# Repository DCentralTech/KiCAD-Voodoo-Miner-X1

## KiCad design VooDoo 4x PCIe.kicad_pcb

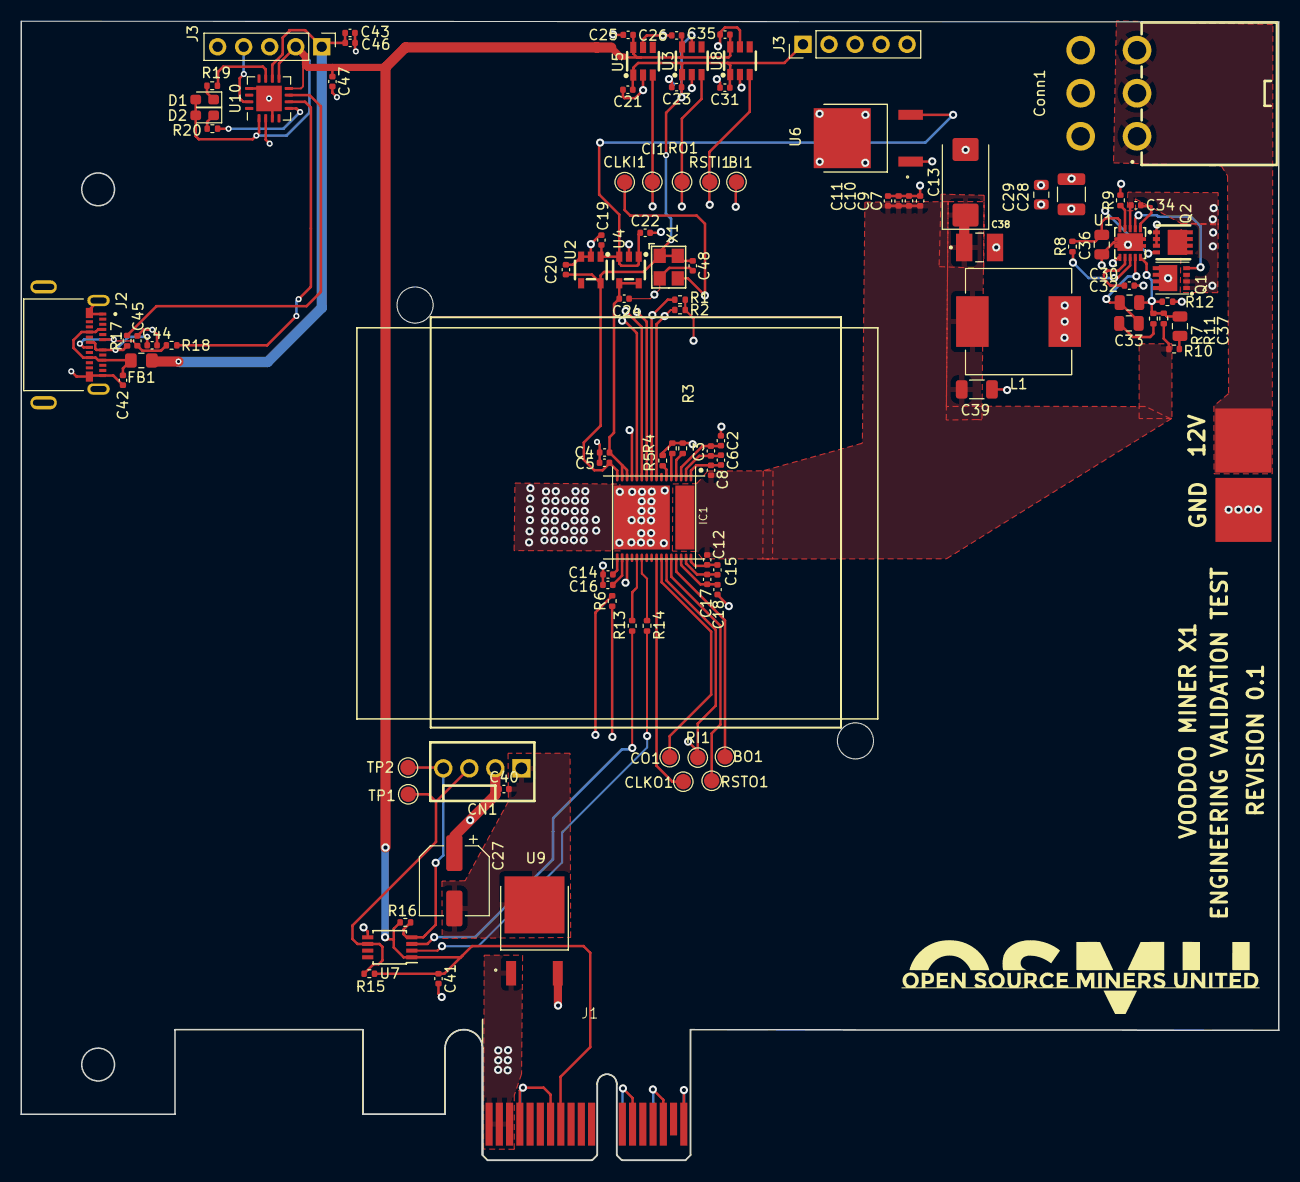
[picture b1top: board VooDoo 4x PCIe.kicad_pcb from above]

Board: 4 copper layers, 122.7 x 111.2 mm, 104 parts (1 on the bottom side), 54 nets.

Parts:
BI1: TestPoint; TestPoint_Pad_D1.5mm
BO1: TestPoint; TestPoint_Pad_D1.5mm
C1: 470pF; C_0402_1005Metric
C2, C3, C4, C5, C6, C8, C10, C11, C12, C14, C15, C16, C17, C18: 587-5514-1-ND; C_0402_1005Metric
C7, C9, C21, C23, C25, C26, C31, C35, C40, C41, C48: 311-3342-1-ND; C_0402_1005Metric
C13: 330uF; CP_EIA-7343-31_Kemet-D_Pad2.25x2.55mm_HandSolder
C19, C22, C24: 1uF; C_0402_1005Metric
C20: 2.2uF; C_0402_1005Metric
C27: 220uF; CP_Elec_6.3x7.7
C28: 10uF; C_1210_3225Metric
C29: 1uF; C_0805_2012Metric
C30: 3.3nF; C_0402_1005Metric
C32: 270pF; C_0805_2012Metric
C33: 1.8nF; C_0805_2012Metric
C34: 0.1uF; C_0402_1005Metric
C36: 4.7uF; C_0805_2012Metric
C37: 680pF; C_0805_2012Metric
C38: 220uF; CAP_2R5TPE220MFGB
C39: 22uF; C_1206_3216Metric
C42: 10nF; C_0402_1005Metric
C43, C47: 100nF; C_0402_1005Metric
C44, C45: 47pF; C_0402_1005Metric
C46: 4.7uF; C_0402_1005Metric
CI1: TestPoint; TestPoint_Pad_D1.5mm
CLKI1: TestPoint; TestPoint_Pad_D1.5mm
CLKO1: TestPoint; TestPoint_Pad_D1.5mm
CN1: HF1004E; CONN-TH_4P-P2.54_HF1004E
CO1: TestPoint; TestPoint_Pad_D1.5mm
Conn1: CONN-TH_HAA420A-6AW
D1: RXLED; LED_0603_1608Metric_Pad1.05x0.95mm_HandSolder
D2: TXLED; LED_0603_1608Metric_Pad1.05x0.95mm_HandSolder
FB1: Ferrite_Bead; L_0805_2012Metric_Pad1.15x1.40mm_HandSolder
IC1: BM1397_mode1; BM1397
J1: PCIexpress_x1; PCIE1XSMALL
J2: USB_C_Receptacle_USB2.0; MOLEX_1054550101
J3, J3#2: Conn_01x05; PinHeader_1x05_P2.54mm_Vertical
L1: 330nH; L_Vishay_IHLP-4040
Q1: CSD17551Q3A; VSONP-8_L3.2-W3.0-P0.65-LS3.3-BL
Q2: CSD17575Q3; VSON-CLIP-8_L3.3-W3.3-P0.65-BL
R1, R2: 1k; R_0402_1005Metric
R3, R4, R5: 0; R_0402_1005Metric
R6, R11, R16: 10k; R_0402_1005Metric
R7: 4.12k; R_0402_1005Metric
R8: 100k; R_0402_1005Metric
R9: 5.9k; R_0402_1005Metric
R10: 1.62k; R_0402_1005Metric
R12: 6.65k; R_0402_1005Metric
R13, R14: 100; R_0402_1005Metric
R15: 5.6k; R_0402_1005Metric
R17, R18: 27R; R_0402_1005Metric
R19, R20: 270R; R_0402_1005Metric
RI1: TestPoint; TestPoint_Pad_D1.5mm
RO1: TestPoint; TestPoint_Pad_D1.5mm
RSTI1: TestPoint; TestPoint_Pad_D1.5mm
RSTO1: TestPoint; TestPoint_Pad_D1.5mm
TP1, TP2: TestPoint; TestPoint_Pad_D1.5mm
U1: TPS40305; VSON-10_L3.0-W3.0-P0.50-BL-EP_TPS62410DRCR
U2: LN1134A182MR-G; SOT-23-5_L3.0-W1.7-P0.95-LS2.8-BR
U3, U5, U8: SN74LVC1T45DBVR; SOT-23-6_L2.9-W1.6-P0.95-LS2.8-BR
U4: SGM2036-ADJYN5G/TR; SOT-23-5_L3.0-W1.7-P0.95-LS2.8-BR
U6, U9: VREG_L7805CDT-TR
U7: EMC2101-R; TSSOP-8_3x3mm_P0.65mm
U10: FT230XQ; QFN-16-1EP_4x4mm_P0.65mm_EP2.5x2.5mm
X1: OT322525MJBA4SL; OSC-SMD_4P-L3.2-W2.5-BL

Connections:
3V3: C25.1, C26.1, C35.1, C41.1, C47.1, D1.2 (A), D2.2 (A), J1.A9 (+3.3V), J1.A10 (+3.3V), J1.B8 (+3.3V), J3#2.2, R15.2, R16.2, U3.6 (VCCB), U5.6 (VCCB), U7.1 (VDD), U8.6 (VCCB), U10.1 (VCCIO), U10.8 (3V3OUT), U10.9 (~RESET)
5V: C19.1, C22.1, C27.1, C40.1, CN1.2, U2.1 (VIN), U4.1 (IN), U4.3 (EN), U6.2, U9.2
+12V: C28.1, C29.1, Conn1.1, Conn1.3, Conn1.5, Q1.5 (D), U1.1 (VDD), U6.1
/Asic/0V8: C4.1, C16.1, C24.1, IC1.14 (PLL_VDD), IC1.15 (VDDIO_08_0), IC1.18 (VDDIO_08_1), U4.4 (BP/FB), U4.5 (OUT)
/Asic/1V8: C5.1, C14.1, C20.1, C21.1, C23.1, C31.1, C48.2, IC1.16 (VDDIO_18_0), IC1.17 (VDDIO_18_1), J3.1, R6.2, U2.5 (VOUT), U3.1 (VCCA), U3.5 (DIR), U5.1 (VCCA), U8.1 (VCCA), X1.1 (EN), X1.4 (VDD)
/Asic/CI: CI1.1, IC1.11 (CI), J3.2, U5.3 (A)
/Asic/RO: IC1.10 (RO), J3.3, RO1.1, U3.3 (A)
/Asic/RST_N: IC1.9 (NRSTI), J3.4, R1.2, RSTI1.1, U8.3 (A)
/DC components/OUT0: C32.2, C37.2, R7.2, R11.2, R12.1, U1.5 (FB)
/DC components/PGOOD: R8.1, U1.3 (PGOOD)
/DC components/SW: C34.2, L1.1, Q1.1, Q1.2, Q1.3 (S), Q2.5 (D), U1.8 (SW)
/FAN/FAN_PWM: CN1.4, R16.1, TP2.1, U7.4 (FAN)
/FAN/FAN_TACH: CN1.3, R15.1, TP1.1, U7.6 (ALERT/TACH)
/ftdi/RXLED: R19.2, U10.11 (CBUS1)
/ftdi/TXLED: R20.2, U10.5 (CBUS2)
GND: C2.1, C4.2, C5.2, C7.2, C9.2, C10.2, C11.2, C13.2, C14.2, C16.2, C18.2, C19.2, C20.2, C21.2, C22.2, C23.2, C24.2, C25.2, C26.2, C27.2, C28.2, C29.2, C30.2, C31.2, C35.2, C36.2, C38.2, C39.2, C40.2, C41.2, C42.2, C43.2, C44.2, C45.2, C46.2, C47.2, C48.1, CN1.1, Conn1.2, Conn1.4, Conn1.6, IC1.13 (PLL_VSS), IC1.19 (VSS), IC1.34 (VSS_0), J1.A4 (GND), J1.A12 (GND), J1.A15 (GND), J1.A18 (GND), J1.B4 (GND), J1.B7 (GND), J1.B13 (GND), J1.B16 (GND), J1.B18 (GND), J2.A1 (GND), J2.A12 (GND), J2.B1 (GND), J2.B12 (GND), J2.S1 (SHIELD), J3.5, J3#2.5, Q2.1, Q2.2, Q2.3 (S), R1.1, R2.1, R3.1, R4.1, R5.1, R9.2, R12.2, U1.11 (GND), U2.2 (VSS), U2.3 (CE), U3.2 (GND), U4.2 (GND), U5.2 (GND), U5.5 (DIR), U6.3, U7.5 (GND), U8.2 (GND), U8.5 (DIR), U9.3, U10.3 (GND), U10.13 (GND), U10.17 (GND), X1.2 (GND)
unnamed: C33.2, R7.1
unnamed: C37.1, R10.2
unnamed: C42.1, FB1.2, J2.A4 (VBUS), J2.A9 (VBUS), J2.B4 (VBUS), J2.B9 (VBUS)
unnamed: C44.1, J2.A7 (D-), J2.B7 (D-), R17.2
unnamed: C45.1, J2.A6 (D+), J2.B6 (D+), R18.1
unnamed: D1.1 (K), R19.1
unnamed: D2.1 (K), R20.1
unnamed: IC1.4 (ADDR0), R3.2
unnamed: IC1.5 (ADDR1), R4.2
unnamed: IC1.6 (ADDR2), R5.2
unnamed: BI1.1, IC1.8 (BI), R2.2
unnamed: BO1.1, IC1.29 (BO)
unnamed: CLKI1.1, IC1.12 (CLKI), X1.3 (OUT)
unnamed: CLKO1.1, IC1.25 (CLKO)
unnamed: CO1.1, IC1.26 (CO)
unnamed: IC1.28 (NRSTO), RSTO1.1
unnamed: IC1.27 (RI), R6.1, RI1.1
unnamed: C2.2, C3.1, IC1.3 (VDD1_0)
unnamed: C17.2, C18.1, IC1.30 (VDD1_1)
unnamed: C3.2, C6.1, IC1.2 (VDD2_0)
unnamed: C15.2, C17.1, IC1.31 (VDD2_1)
unnamed: C6.2, C8.1, IC1.1 (VDD3_0)
unnamed: C12.2, C15.1, IC1.32 (VDD3_1)
unnamed: Q1.4 (G), U1.7 (HDRV)
unnamed: Q2.4 (G), R9.1, U1.9 (LDRV)
unnamed: C34.1, U1.6 (BOOT)
unnamed: C36.1, R8.2, U1.10 (BP)
unnamed: C32.1, C33.1, U1.4 (COMP)
unnamed: C30.1, U1.2 (SS)
unnamed: R17.1, U10.7 (USBDM)
unnamed: R18.2, U10.6 (USBDP)
PC12V: J1.A2 (+12V), J1.A3 (+12V), J1.B1 (+12V), J1.B2 (+12V), J1.B3 (+12V), U9.1
RX: J3#2.3, U10.2 (RXD)
TEMP_N: C1.2, IC1.21 (TEMP_N), R13.1, R13.2, U7.3 (DN)
TEMP_P: C1.1, IC1.22 (TEMP_P), R14.1, R14.2, U7.2 (DP)
TX: J3#2.4, U10.15 (TXD)
VCC: C43.1, C46.1, FB1.1, J3#2.1, U10.10 (VCC)
VDD: C7.1, C8.2, C9.1, C10.1, C11.1, C12.1, C13.1, C38.1, C39.1, IC1.33 (VDD), L1.2, R10.1, R11.1

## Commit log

2023-06-16 VooDoo Miner X1 [WIP]
    Based on the Bitaxe project by Skot, This is a single BM1397 miner, utilizing the PCIe slot inside your computer!
2023-06-16 Voodoo Miner X1 WIP
    Updated Nets and base routing is 99% done
